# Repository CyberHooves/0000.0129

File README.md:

# 0000.0129
Isolated half-bridge gate driver for IGBTs or MOSFETs

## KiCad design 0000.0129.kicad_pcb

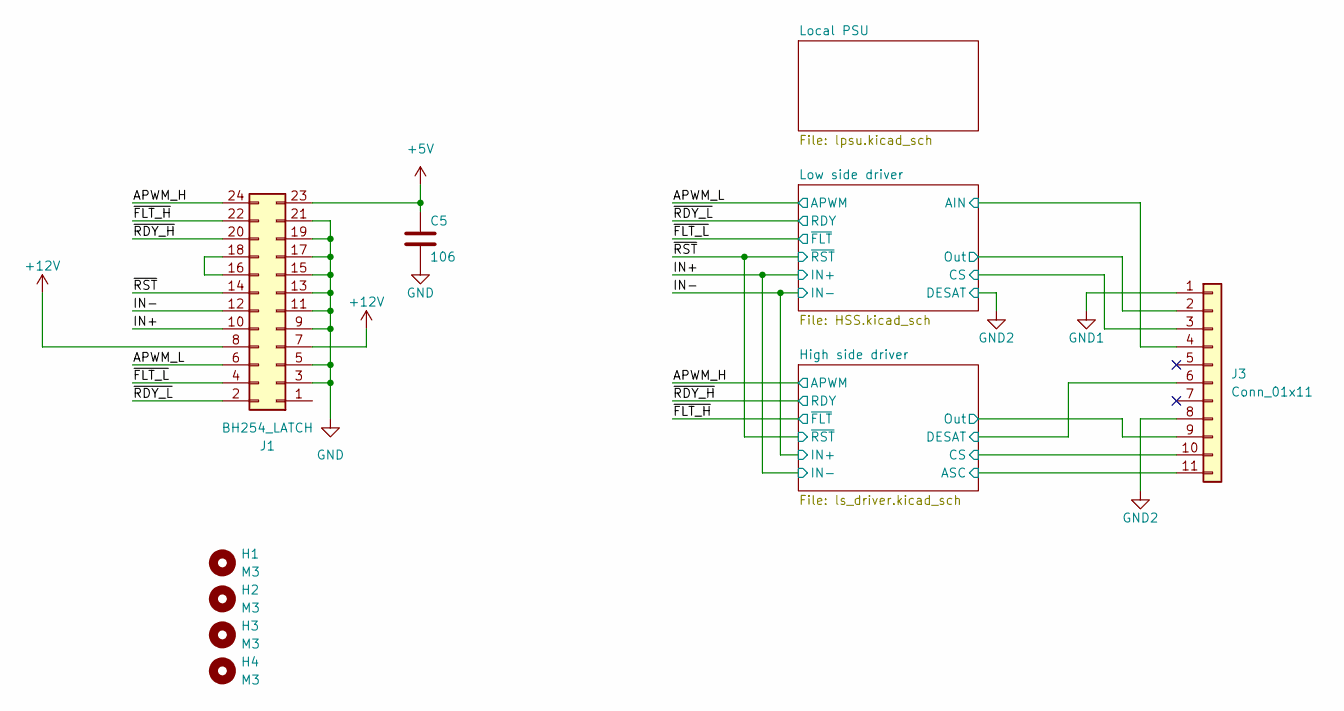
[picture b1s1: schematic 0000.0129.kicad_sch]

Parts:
C5: 106; C_0805_2012Metric
H1, H2, H3, H4: M3; MountingHole_3.2mm_M3_Pad
J1: BH254_LATCH; IDC-Header_2x12_P2.54mm_Latch9.5mm_Vertical
J3: Conn_01x11; PhoenixContact_MC_1,5_11-GF-5.08_1x11_P5.08mm_Horizontal_Th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

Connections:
+5V: C5.1, J1.23; also elsewhere on the board
+12V: J1.7, J1.8; also elsewhere on the board
/APWM_H: J1.24; also elsewhere on the board
/APWM_L: J1.6; also elsewhere on the board
/High side driver/ASC: J3.11; also elsewhere on the board
/High side driver/CS: J3.10; also elsewhere on the board
/High side driver/DESAT: J3.6; also elsewhere on the board
/High side driver/Out: J3.9; also elsewhere on the board
/IN+: J1.10; also elsewhere on the board
/IN-: J1.12; also elsewhere on the board
/Low side driver/AIN: J3.4; also elsewhere on the board
/Low side driver/CS: J3.3; also elsewhere on the board
/Low side driver/Out: J3.2; also elsewhere on the board
/~FLT_H: J1.22; also elsewhere on the board
/~FLT_L: J1.4; also elsewhere on the board
/~RDY_H: J1.20; also elsewhere on the board
/~RDY_L: J1.2; also elsewhere on the board
/~RST: J1.14; also elsewhere on the board
GND: C5.2, J1.3, J1.5, J1.9, J1.11, J1.13, J1.15, J1.17, J1.19, J1.21; also elsewhere on the board
GND1: J3.1; also elsewhere on the board
GND2: J3.8; also elsewhere on the board
unnamed: J1.16, J1.18

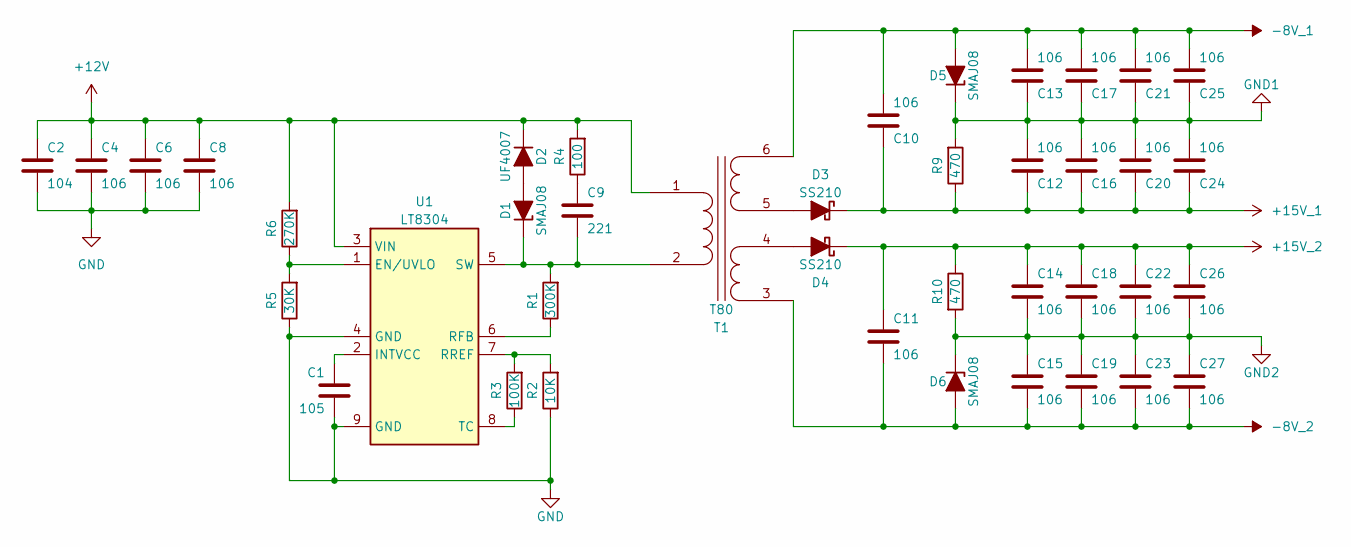
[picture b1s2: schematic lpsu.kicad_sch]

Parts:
C1: 105; C_0805_2012Metric
C2: 104; R_0805_2012Metric
C4, C6, C8, C10, C11, C12, C13, C14, C15, C16, C17, C18, C19, C20, C21, C22, C23, C24, C25, C26, C27: 106; C_1210_3225Metric
C9: 221; C_0805_2012Metric
D1, D5, D6: SMAJ08; D_SMA
D2: UF4007; D_SOD-123
D3, D4: SS210; D_SMB
R1: 300K; R_0805_2012Metric
R2: 10K; R_0805_2012Metric
R3: 100K; R_0805_2012Metric
R4: 100; R_2512_6332Metric
R5: 30K; R_0805_2012Metric
R6: 270K; R_0805_2012Metric
R9, R10: 470; R_1210_3225Metric
T1: T80; TRANSFORMER_T80_6P_01_H
U1: LT8304; SOIC-8-1EP_3.9x4.9mm_P1.27mm_EP2.41x3.3mm

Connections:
+12V: C2.1, C4.1, C6.1, C8.1, D2.1 (K), R4.2, R6.2, T1.1 (AB), U1.3 (VIN); also elsewhere on the board
+15V_1: C10.1, C12.1, C16.1, C20.1, C24.1, D3.1 (K), R9.1; also elsewhere on the board
+15V_2: C11.1, C14.1, C18.1, C22.1, C26.1, D4.1 (K), R10.1; also elsewhere on the board
-8V_1: C10.2, C13.2, C17.2, C21.2, C25.2, D5.2 (A), T1.6 (SD); also elsewhere on the board
-8V_2: C11.2, C15.2, C19.2, C23.2, C27.2, D6.2 (A), T1.3 (SA); also elsewhere on the board
GND: C1.2, C2.2, C4.2, C6.2, C8.2, R2.1, R5.1, U1.4 (GND), U1.9 (GND); also elsewhere on the board
GND1: C12.2, C13.1, C16.2, C17.1, C20.2, C21.1, C24.2, C25.1, D5.1 (K), R9.2; also elsewhere on the board
GND2: C14.2, C15.1, C18.2, C19.1, C22.2, C23.1, C26.2, C27.1, D6.1 (K), R10.2; also elsewhere on the board
unnamed: C9.1, R4.1
unnamed: D1.2 (A), D2.2 (A)
unnamed: C9.2, D1.1 (K), R1.2, T1.2 (AA), U1.5 (SW)
unnamed: D3.2 (A), T1.5 (SC)
unnamed: D4.2 (A), T1.4 (SB)
unnamed: R5.2, R6.1, U1.1 (EN/UVLO)
unnamed: C1.1, U1.2 (INTVCC)
unnamed: R1.1, U1.6 (RFB)
unnamed: R2.2, R3.2, U1.7 (RREF)
unnamed: R3.1, U1.8 (TC)

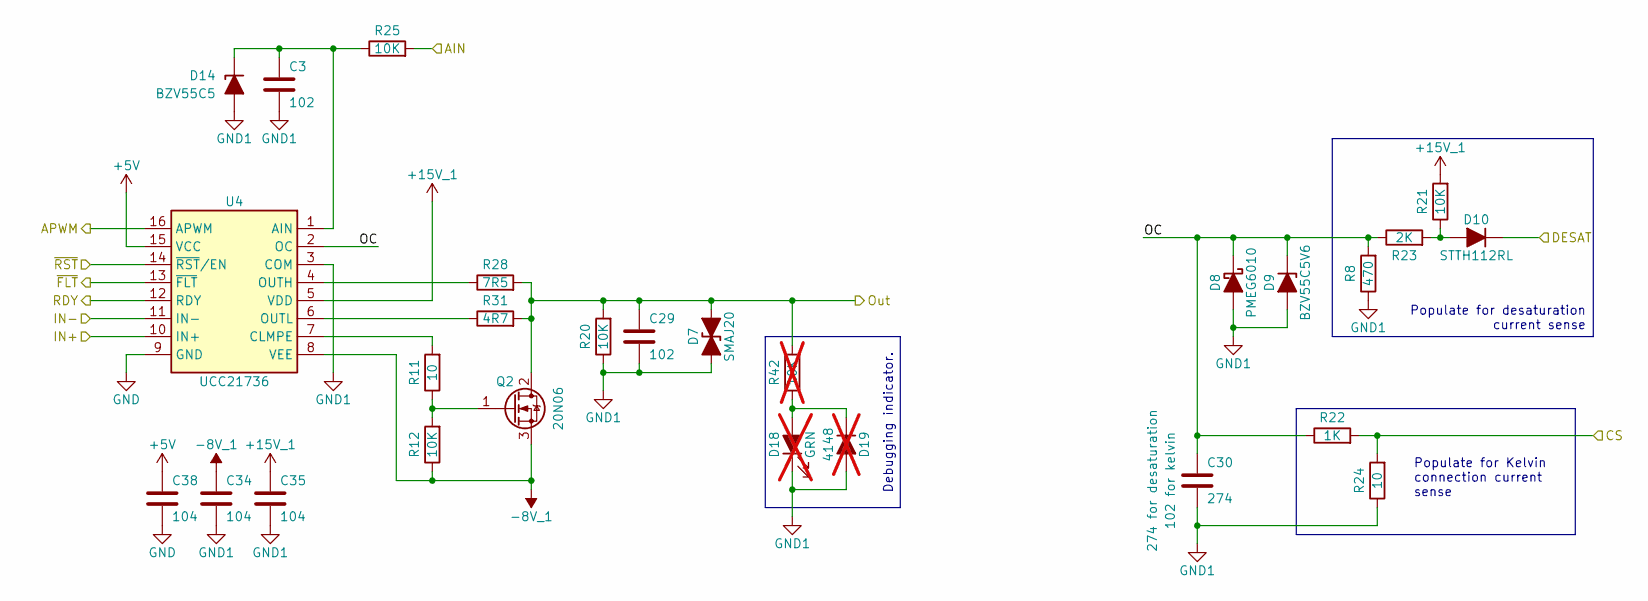
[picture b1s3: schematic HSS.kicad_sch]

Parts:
C3, C29: 102; C_0805_2012Metric
C30: 274; C_0805_2012Metric
C34, C35, C38: 104; C_0805_2012Metric
D7: SMAJ20; D_SMA
D8: PMEG6010; D_SOD-123
D9: BZV55C5V6; D_SOD-123
D10: STTH112RL; D_DO-41_SOD81_P10.16mm_Horizontal
D14: BZV55C5; D_SOD-123
D18: GRN; LED_D3.0mm; not fitted
D19: 4148; D_SOD-123; not fitted
Q2: 20N06; TO-252-2
R8: 470; R_0805_2012Metric
R11: 10; R_0805_2012Metric
R12, R20, R21: 10K; R_0805_2012Metric
R22: 1K; R_0805_2012Metric
R23: 2K; R_0805_2012Metric
R24: 10; R_2512_6332Metric
R25: 10K; R_1210_3225Metric
R28: 7R5; R_Axial_DIN0617_L17.0mm_D6.0mm_P20.32mm_Horizontal
R31: 4R7; R_Axial_DIN0617_L17.0mm_D6.0mm_P20.32mm_Horizontal
R42: 10K; R_0805_2012Metric; not fitted
U4: UCC21736; SOIC-16W_7.5x10.3mm_P1.27mm

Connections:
+5V: C38.1, U4.15 (VCC); also elsewhere on the board
+15V_1: C35.1, R21.2, U4.5 (VDD); also elsewhere on the board
-8V_1: C34.1, Q2.3 (S), R12.1, U4.8 (VEE); also elsewhere on the board
/APWM_L: U4.16 (APWM); also elsewhere on the board
/IN+: U4.10 (IN+); also elsewhere on the board
/IN-: U4.11 (IN-); also elsewhere on the board
/Low side driver/AIN: R25.2; also elsewhere on the board
/Low side driver/CS: R22.2, R24.2; also elsewhere on the board
/Low side driver/OC: C30.1, D8.1 (K), D9.1 (K), R8.2, R22.1, R23.1, U4.2 (OC)
/Low side driver/Out: C29.1, D7.2 (A2), Q2.2 (D), R20.2, R28.2, R31.2, R42.2; also elsewhere on the board
/~FLT_L: U4.13 (~FLT); also elsewhere on the board
/~RDY_L: U4.12 (RDY); also elsewhere on the board
/~RST: U4.14 (~RST/EN); also elsewhere on the board
GND: C38.2, U4.9 (GND); also elsewhere on the board
GND1: C3.2, C29.2, C30.2, C34.2, C35.2, D7.1 (A1), D8.2 (A), D9.2 (A), D14.2 (A), D18.1 (K), D19.2 (A), R8.1, R20.1, R24.1, U4.3 (COM); also elsewhere on the board
GND2: D10.1 (K); also elsewhere on the board
unnamed: D10.2 (A), R21.1, R23.2
unnamed: C3.1, D14.1 (K), R25.1, U4.1 (AIN)
unnamed: D18.2 (A), D19.1 (K), R42.1
unnamed: Q2.1 (G), R11.1, R12.2
unnamed: R11.2, U4.7 (CLMPE)
unnamed: R28.1, U4.4 (OUTH)
unnamed: R31.1, U4.6 (OUTL)

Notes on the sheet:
Populate for Kelvin connection current sense
Populate for desaturation current sense
Debugging indicator.

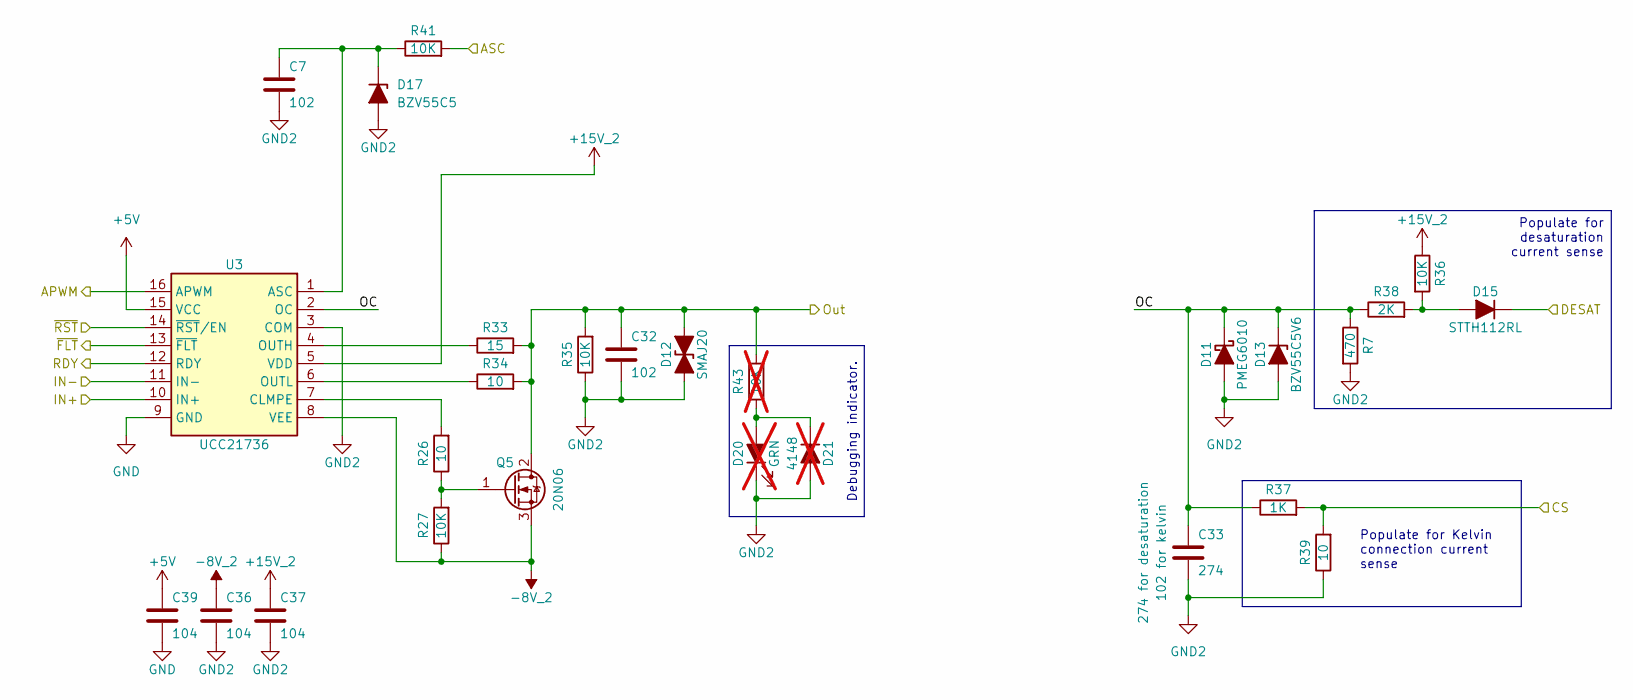
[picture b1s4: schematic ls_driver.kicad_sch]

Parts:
C7, C32: 102; C_0805_2012Metric
C33: 274; C_0805_2012Metric
C36, C37, C39: 104; C_0805_2012Metric
D11: PMEG6010; D_SOD-123
D12: SMAJ20; D_SMA
D13: BZV55C5V6; D_SOD-123
D15: STTH112RL; D_DO-41_SOD81_P10.16mm_Horizontal
D17: BZV55C5; D_SOD-123
D20: GRN; LED_D3.0mm; not fitted
D21: 4148; D_SOD-123; not fitted
Q5: 20N06; TO-252-2
R7: 470; R_0805_2012Metric
R26: 10; R_0805_2012Metric
R27, R35, R36: 10K; R_0805_2012Metric
R33: 15; R_Axial_DIN0617_L17.0mm_D6.0mm_P20.32mm_Horizontal
R34: 10; R_Axial_DIN0617_L17.0mm_D6.0mm_P20.32mm_Horizontal
R37: 1K; R_0805_2012Metric
R38: 2K; R_0805_2012Metric
R39: 10; R_2512_6332Metric
R41: 10K; R_1210_3225Metric
R43: 10K; R_0805_2012Metric; not fitted
U3: UCC21736; SOIC-16W_7.5x10.3mm_P1.27mm

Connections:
+5V: C39.1, U3.15 (VCC); also elsewhere on the board
+15V_2: C37.1, R36.1, U3.5 (VDD); also elsewhere on the board
-8V_2: C36.1, Q5.3 (S), R27.1, U3.8 (VEE); also elsewhere on the board
/APWM_H: U3.16 (APWM); also elsewhere on the board
/High side driver/ASC: R41.2; also elsewhere on the board
/High side driver/CS: R37.2, R39.2; also elsewhere on the board
/High side driver/DESAT: D15.1 (K); also elsewhere on the board
/High side driver/OC: C33.1, D11.1 (K), D13.1 (K), R7.1, R37.1, R38.1, U3.2 (OC)
/High side driver/Out: C32.1, D12.2 (A2), Q5.2 (D), R33.2, R34.2, R35.2, R43.2; also elsewhere on the board
/IN+: U3.11 (IN-); also elsewhere on the board
/IN-: U3.10 (IN+); also elsewhere on the board
/~FLT_H: U3.13 (~FLT); also elsewhere on the board
/~RDY_H: U3.12 (RDY); also elsewhere on the board
/~RST: U3.14 (~RST/EN); also elsewhere on the board
GND: C39.2, U3.9 (GND); also elsewhere on the board
GND2: C7.2, C32.2, C33.2, C36.2, C37.2, D11.2 (A), D12.1 (A1), D13.2 (A), D17.2 (A), D20.1 (K), D21.2 (A), R7.2, R35.1, R39.1, U3.3 (COM); also elsewhere on the board
unnamed: D15.2 (A), R36.2, R38.2
unnamed: C7.1, D17.1 (K), R41.1, U3.1 (ASC)
unnamed: D20.2 (A), D21.1 (K), R43.1
unnamed: Q5.1 (G), R26.1, R27.2
unnamed: R26.2, U3.7 (CLMPE)
unnamed: R33.1, U3.4 (OUTH)
unnamed: R34.1, U3.6 (OUTL)

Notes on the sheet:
Populate for Kelvin connection current sense
Debugging indicator.
Populate for desaturation current sense

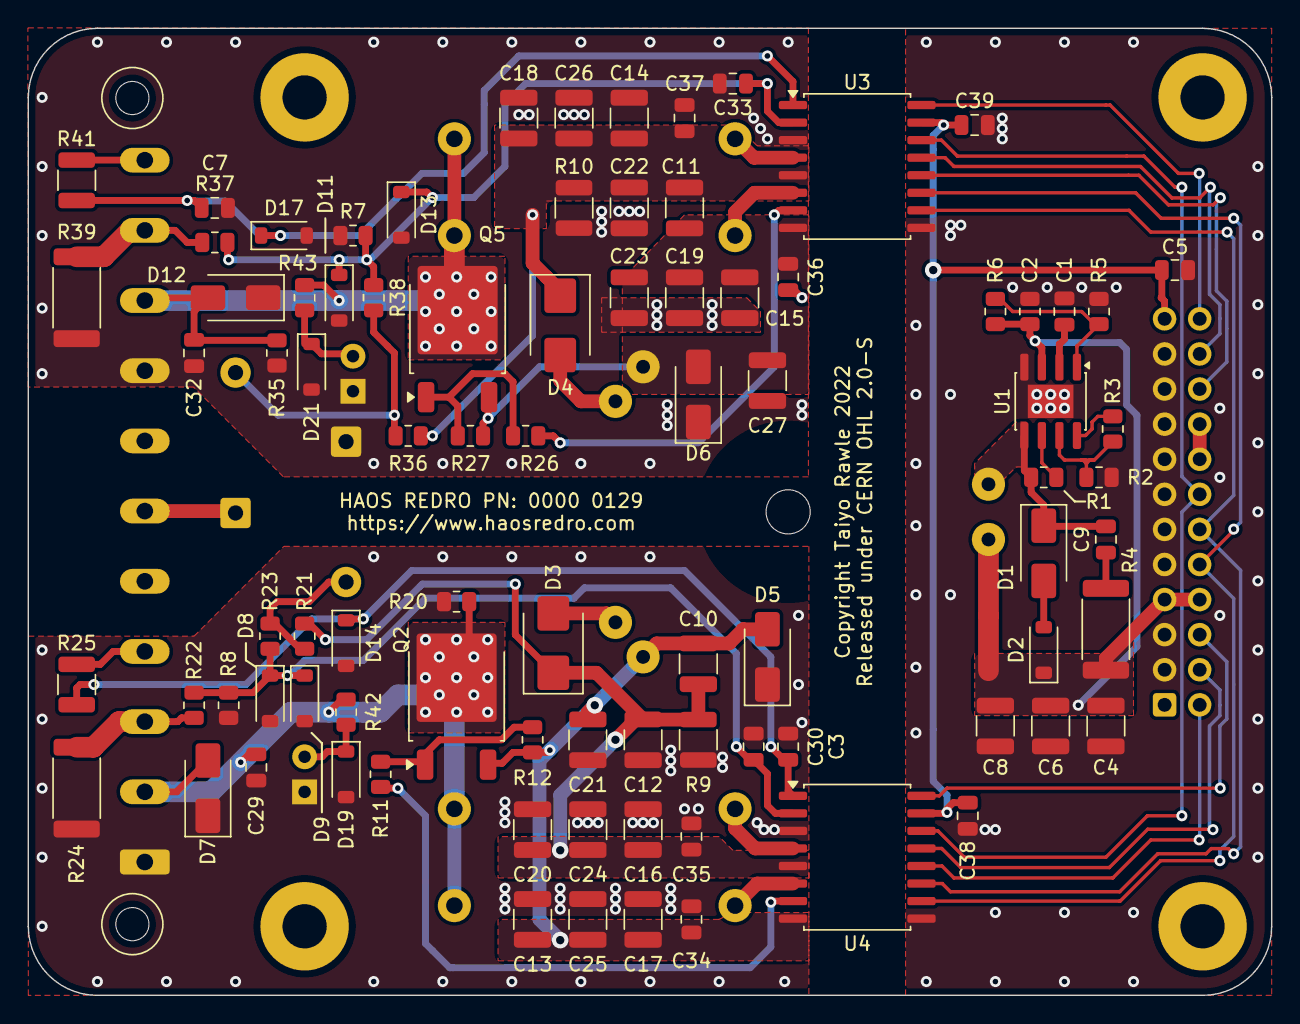
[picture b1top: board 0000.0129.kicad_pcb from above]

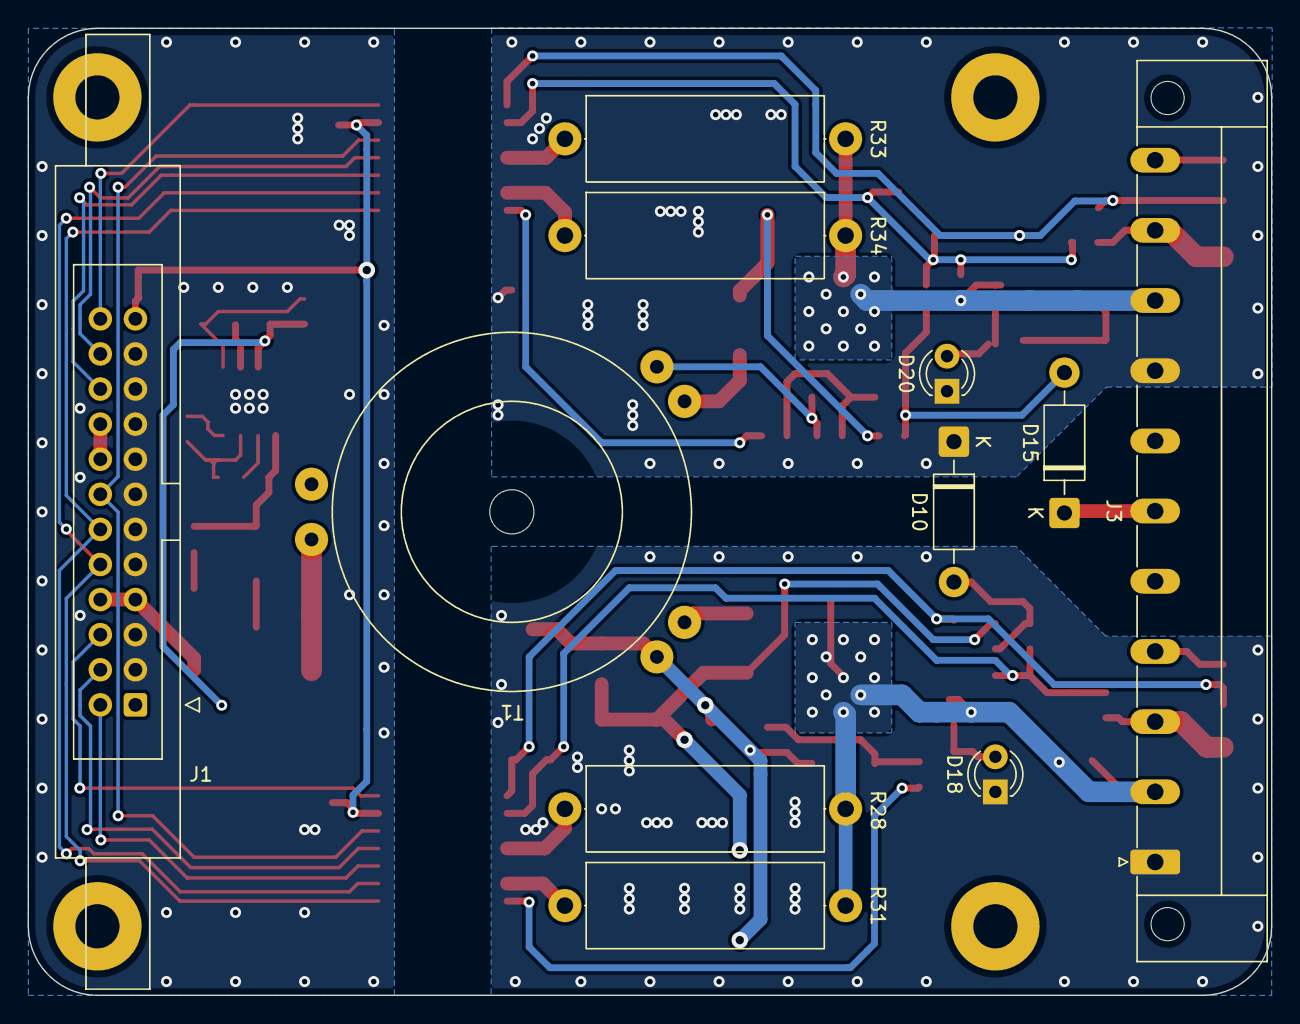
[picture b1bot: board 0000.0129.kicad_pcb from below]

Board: 2 copper layers, 90.0 x 70.0 mm, 101 parts (11 on the bottom side), 52 nets.

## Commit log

2025-10-24 PCB updated - screw hole clearances were incorrect.

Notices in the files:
0000.0129.kicad_pcb:
Copyright Taiyo Rawle 2022
Released under CERN OHL 2.0-S
